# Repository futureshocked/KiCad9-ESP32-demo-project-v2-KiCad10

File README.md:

# KiCad ESP32 demo project, iteration 2 (KiCad 10)

This repository holds the second, corrected iteration of the ESP32 sensor board from my KiCad 9 video lectures, updated and saved in **KiCad 10**. If you want to study the design, modify it or have it manufactured, start here. One known issue remains: automatic reset and download mode do not work, so you upload firmware with the Boot and Reset buttons or through the ESP32-C3's built-in USB. See [Known issue](#known-issue-automatic-reset-and-download-mode-do-not-work).

The first iteration, which matches the original lectures and contains the errors described below, is archived in **[KiCad9-ESP32-demo-project-v1](https://github.com/futureshocked/KiCad9-ESP32-demo-project-v1)**.

## About the project

The board is a battery-powered environmental sensor built around the ESP32-C3. It is a four-layer PCB, about 81 × 54 mm, and includes:

1. An ESP32-C3-WROOM-02 module (U3) with Wi-Fi and Bluetooth LE.
2. A USB-C connector with a CP2102N USB-to-UART bridge (U4), USBLC6-2SC6 ESD protection (U5) and automatic boot/reset circuitry (Q2, Q3).
3. An MCP73871 Li-ion charger with power-path management (U1), a PTC fuse on its output (F2) and an LM1117 3.3 V regulator (VR1).
4. A BME280 temperature, humidity and pressure sensor (U2).
5. A TEMT6000 ambient light sensor (Q1).
6. An electret microphone with a MAX4466 amplifier (U7, MK1) and a gain trimmer (R17).
7. A microSD card slot (J3) and a W25Q32 SPI flash chip (U6).
8. A header for an I2C OLED display, status LEDs, and Boot and Reset buttons.

**You need KiCad 10 or later to open these files.** They are saved in the KiCad 10 file format, which KiCad 9 cannot read. The project files are still named `KiCad 9 ESP32 demo project` so that they match the lectures.

## Two repositories, and why

There are two repositories for this project:

| Repository | Contents | Use it to |
|---|---|---|
| **[KiCad9-ESP32-demo-project-v1](https://github.com/futureshocked/KiCad9-ESP32-demo-project-v1)** | Iteration 1: the original KiCad 9 files with known errors, and a focused repair of U2, U4 and the microphone output | Follow the original lectures and the repair video, and see how the project developed |
| **KiCad9-ESP32-demo-project-v2-KiCad10** (this one) | Iteration 2, corrected and updated in KiCad 10 | Study, modify or manufacture the board |

I have kept both so that the history of the project stays intact, while anyone who wants to experiment with the design, or have it made, has a clean and correct version to start from.

## Status of the issues found in iteration 1

| Issue | Status in iteration 2 |
|---|---|
| 1. PCB out of sync with the schematic (U2, U4, U5, C15) | **Fixed** |
| 2. Microphone output on an ADC2 pin | **Fixed** |
| 3. Automatic reset and download mode (auto-program circuit) | **Partly fixed, still not working.** Q3 is corrected, but DTR is still connected to an input pin. See [Known issue](#known-issue-automatic-reset-and-download-mode-do-not-work). |

1. **The PCB was out of sync with the schematic.** In iteration 1, nine pads on U4 (CP2102N), U5 (USBLC6), U2 (BME280) and C15 were on +3.3V instead of GND, USB D- or VBUS sense. In this version the PCB was updated from the schematic, the stray +3.3V tracks were removed, and those pads were rerouted to their correct nets.
2. **The microphone output was on GPIO5, an ADC2 pin.** Espressif's ESP32-C3 errata recommends against using ADC2. MIC_OUT is now on GPIO0 (ADC1), and CS_SD moved to GPIO5.
3. **Q3 in the auto-program circuit was wired backwards.** Its collector now connects to BOOT and its emitter to DTR, matching Q2 and Espressif's reference circuit. This correction is necessary but not sufficient, because of the issue described next.

The iteration 1 README describes each problem in detail.

## Known issue: automatic reset and download mode do not work

The auto-program circuit (Q2, Q3, R33, R34) is meant to let the CP2102N's DTR and RTS signals reset the ESP32-C3 and put it into download mode, so that you can upload firmware without pressing any buttons. It needs both DTR and RTS to be outputs from the CP2102N.

The CP2102N in this design is the 20-pin QFN package, which has no DTR pin. The net named DTR is connected to U4 pin 15, which is CTS, an input (see table 5.3 of the CP2102N datasheet in `Datasheets/`). Nothing drives the DTR net, so neither automatic reset nor automatic download mode can be relied on. The same mistake is in iteration 1. DRC cannot detect it, because the schematic and PCB agree with each other.

I have not yet decided whether to change the circuit. Until then, use one of these two methods to upload firmware:

1. **Through the USB-C connector and the CP2102N, with the buttons.** Hold **Boot** (S1), press and release **Reset** (S2), then release **Boot**. The ESP32-C3 starts in download mode and you can upload. Press **Reset** afterwards to run the new firmware. Serial monitoring through the CP2102N works normally.
2. **Through the ESP32-C3's built-in USB Serial/JTAG controller.** The ESP32-C3 has its own USB interface on GPIO18 (D-) and GPIO19 (D+). On this board these pins are brought out to header **J5**: pin 3 is D-, pin 4 is D+ and pin 5 is GND. Wire a USB cable's D-, D+ and GND to those pins and power the board from the USB-C connector or the battery. **Do not connect the cable's 5 V wire to J5**: J5 pin 1 is the 3.3 V rail. Through this interface, esptool and the Arduino and ESP-IDF tools can reset the chip and enter download mode without the buttons, and you get a serial console and JTAG debugging as well. For this to keep working, your firmware must not use GPIO18 and GPIO19 as ordinary I/O.

## Other changes from iteration 1

1. A PTC fuse (F2) on the +5 V output of the charger.
2. A trimmer (R17) to adjust the microphone gain, with new values for R30 (1 kΩ), R31 (22 kΩ) and C19 (10 µF).
3. The light sensor was rearranged so that its output rises with light: Q1's collector goes to +3.3V and R23 pulls the output down to GND.
4. Three extra capacitors: C23 (100 nF decoupling) and C24 and C25 (10 nF filtering on the light sensor signal).
5. The Boot and Reset buttons (S1, S2) were rotated 180°, and the right edge of the board moved about 0.8 mm.

## Design check status

A DRC with **Test for parity between PCB and schematic** enabled reports no errors and no unconnected pads. DRC only compares the PCB with the schematic, so it cannot detect design errors like the DTR problem above. A few warnings remain. None of them affect how the circuit works:

1. **S1 and S2 parity warnings.** The schematic symbols for the Boot and Reset buttons still name the E-Switch TL3305 footprint, while the PCB uses the TE USLPT2819. The two parts number their pins differently, so DRC reports four pad net conflicts. According to the USLPT2819 datasheet, pins 1 and 2 are connected internally, as are pins 3 and 4, and the switch closes between the two pairs. On the PCB, pins 1 and 2 go to GND and pins 3 and 4 go to BOOT or EN, which is correct for the switch that is actually fitted.
2. **USB D- track width.** D- is routed at 0.254 mm and D+ at 0.2 mm. At USB 2.0 full speed (12 Mbit/s) this makes no practical difference, but the two lines are not a matched differential pair.
3. **Housekeeping warnings.** These are library footprint differences, unmirrored text on the back layer, three logo footprints without schematic symbols, two empty description fields, and an "exclude from BOM" setting on J3 that differs between schematic and PCB.

## Files

1. `KiCad 9 ESP32 demo project.kicad_pro`, `.kicad_sch` and `.kicad_pcb`: the KiCad project, with the sub-sheets `esp32-c3-02.kicad_sch`, `sensors.kicad_sch` and `user_interface.kicad_sch`.
2. `Libraries/`: project-specific symbols, footprints and 3D models.
3. `Gerbers/`: Gerber and Excellon drill files, generated from this PCB with the board's saved plot settings.
4. `BOM2.ods`: the bill of materials.
5. `Datasheets/`: datasheets for the main components.
6. `3Dmodel.stl`: an STL export of the board's 3D model, made in March 2025, before the final KiCad 10 edits.

## License

Copyright © 2025–2026, Peter Dalmaris. Licensed under the CERN-OHL-S v2.0. See [LICENSE](LICENSE).

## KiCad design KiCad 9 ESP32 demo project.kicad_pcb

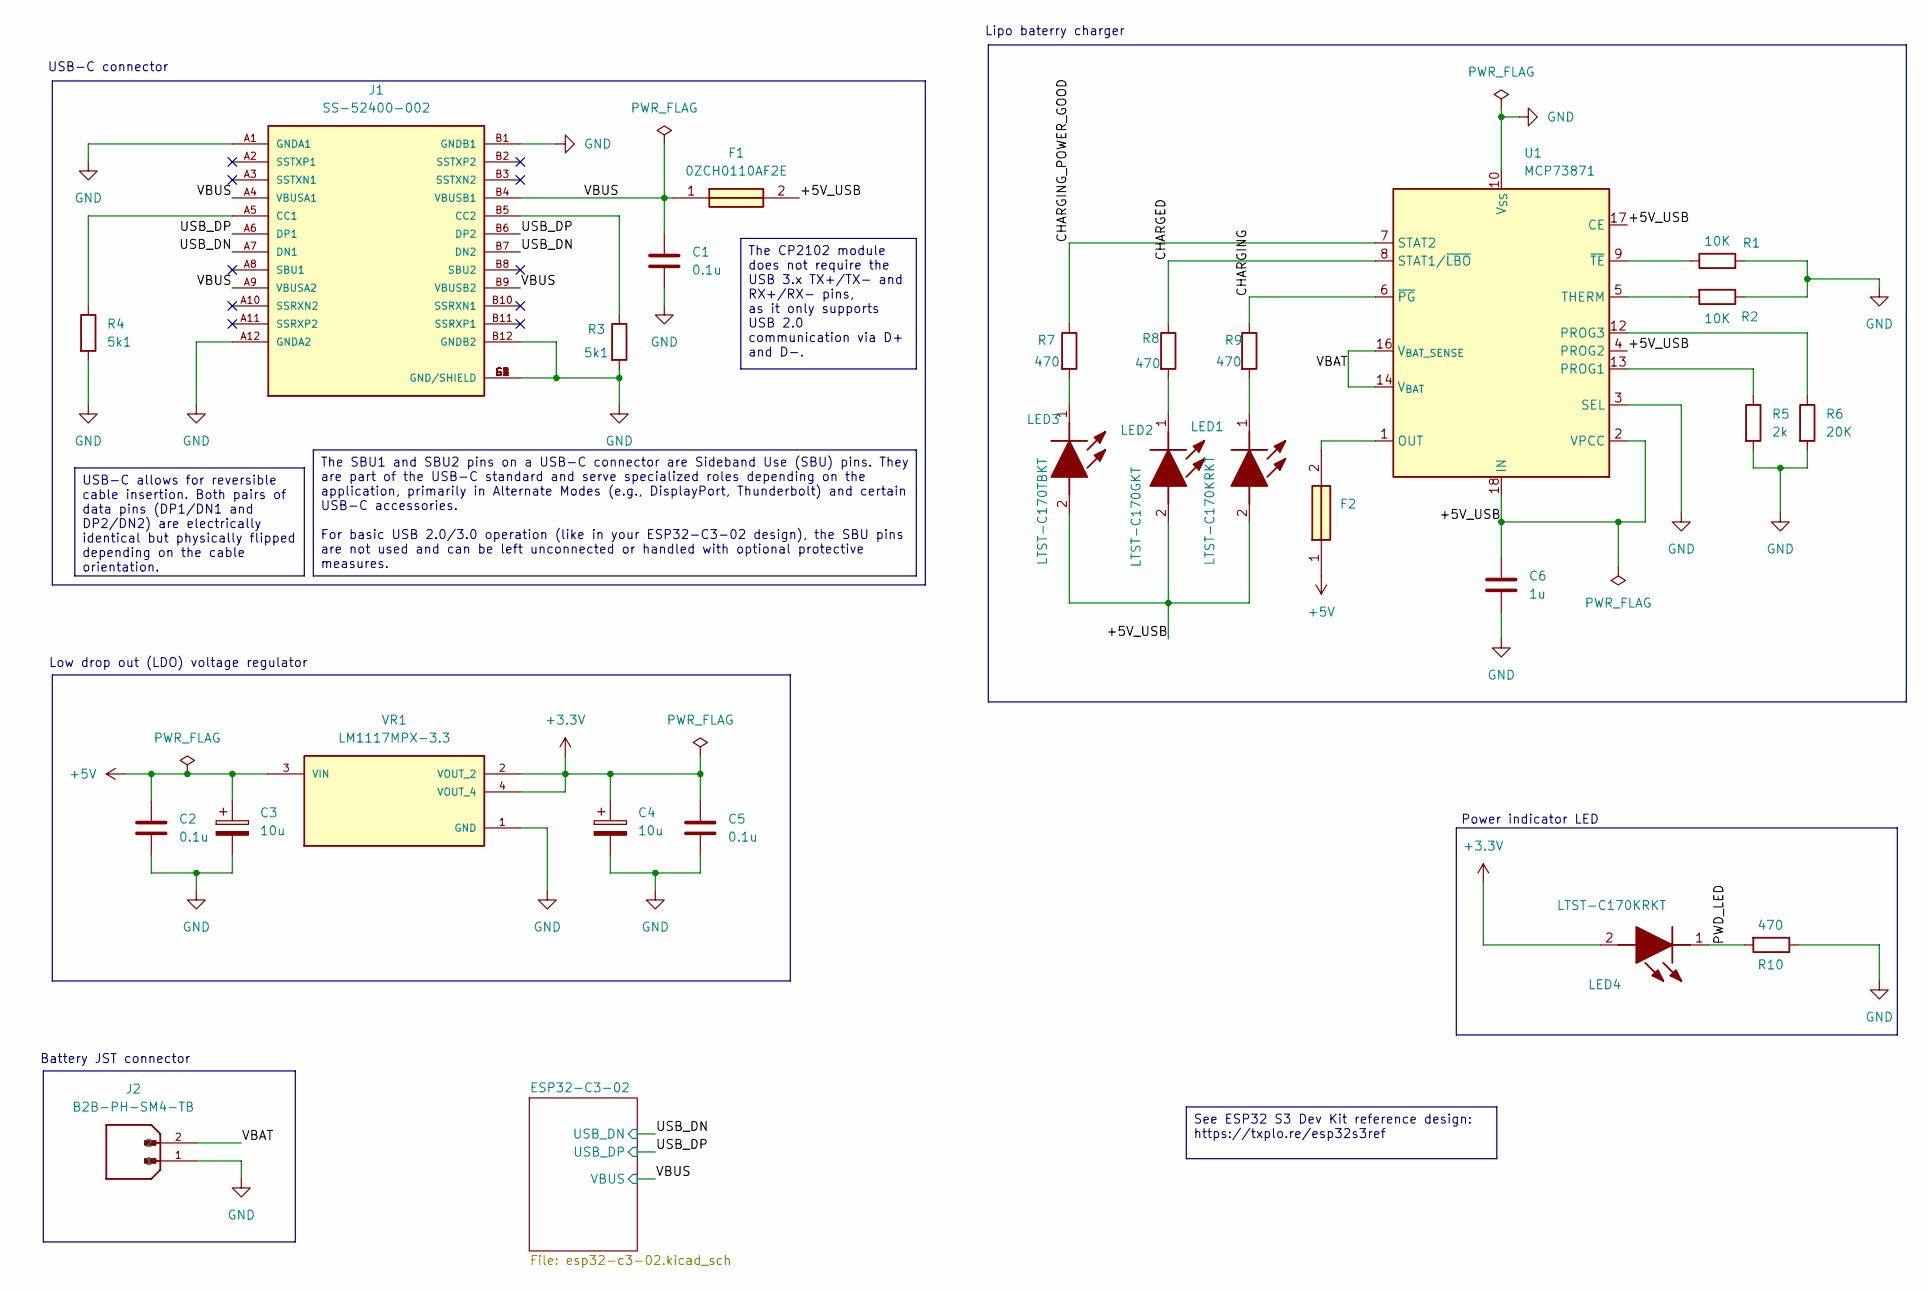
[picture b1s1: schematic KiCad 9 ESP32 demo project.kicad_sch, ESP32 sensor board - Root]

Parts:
C1, C2, C5: 0.1u; C_0805_2012Metric
C3, C4: 10u; T491A
C6: 1u; C_0805_2012Metric
F1, F2: 0ZCH0110AF2E; FUSC3226X100N; Manufacturer_Part_Number 0ZCH0110AF2E
J1: SS-52400-002; BELFUSE_SS-52400-002; PARTREV A0
J2: B2B-PH-SM4-TB; JST_B2B-PH-SM4-TB; PARTREV N/A
LED1, LED4: LTST-C170KRKT; LEDC2012X120N; Manufacturer_Part_Number LTST-C170KRKT; Mouser Part Number 859-LTST-C170KRKT
LED2: LTST-C170GKT; LEDC2012X120N; Manufacturer_Part_Number LTST-C170GKT; Mouser Part Number 859-LTST-C170GKT
LED3: LTST-C170TBKT; LEDC2012X120N; Manufacturer_Part_Number LTST-C170TBKT; Mouser Part Number 859-LTST-C170TBKT
R1, R2: 10K; R_0805_2012Metric
R3, R4: 5k1; R_0805_2012Metric
R5: 2k; R_0805_2012Metric
R6: 20K; R_0805_2012Metric
R7, R8, R9, R10: 470; R_0805_2012Metric
U1: MCP73871; QFN-20-1EP_4x4mm_P0.5mm_EP2.5x2.5mm
VR1: LM1117MPX-3.3; VREG_LM1117MPX-3.3

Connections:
+3.3V: C4.1, C5.1, LED4.2 (A), VR1.2 (VOUT_2), VR1.4 (VOUT_4); also elsewhere on the board
+5V: C2.1, C3.1, F2.1, VR1.3 (VIN)
/+5V_USB: C6.1, F1.2, LED1.2 (A), LED2.2 (A), LED3.2 (A), U1.2 (VPCC), U1.4 (PROG2), U1.17 (CE), U1.18 (IN), U1.19 (IN)
/CHARGED: R8.1, U1.8 (STAT1/~LBO)
/CHARGING: R9.1, U1.6 (~PG)
/CHARGING_POWER_GOOD: R7.1, U1.7 (STAT2)
/PWD_LED: LED4.1 (K), R10.2
/USB_DN: J1.A7 (DN1), J1.B7 (DN2); also elsewhere on the board
/USB_DP: J1.A6 (DP1), J1.B6 (DP2); also elsewhere on the board
/VBAT: J2.2, U1.14 (V_{BAT}), U1.15 (V_{BAT}), U1.16 (V_{BAT_SENSE})
/VBUS: C1.1, F1.1, J1.A4 (VBUSA1), J1.A9 (VBUSA2), J1.B4 (VBUSB1), J1.B9 (VBUSB2); also elsewhere on the board
unnamed: F2.2, U1.1 (OUT), U1.20 (OUT)
unnamed: J1.A5 (CC1), R4.1
unnamed: J1.B5 (CC2), R3.1
unnamed: LED1.1 (K), R9.2
unnamed: LED2.1 (K), R8.2
unnamed: LED3.1 (K), R7.2
unnamed: R5.1, U1.13 (PROG1)
unnamed: R6.1, U1.12 (PROG3)
unnamed: R2.2, U1.5 (THERM)
unnamed: R1.1, U1.9 (~TE)

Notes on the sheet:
Lipo baterry charger
Low drop out (LDO) voltage regulator
Power indicator LED
Battery JST connector
USB-C connector
See ESP32 S3 Dev Kit reference design: https://txplo.re/esp32s3ref
The CP2102 module does not require the USB 3.x TX+/TX- and RX+/RX- pins, as it only supports USB 2.0 communication via D+ and D-.
USB-C allows for reversible cable insertion. Both pairs of data pins (DP1/DN1 and DP2/DN2) are electrically identical but physically flipped depending on the cable orientation.
The SBU1 and SBU2 pins on a USB-C connector are Sideband Use (SBU) pins. They are part of the USB-C standard and serve specialized roles depending on the application, primarily in Alternate Modes (e.g., DisplayPort, Thunderbolt) and certain USB-C accessories. For basic USB 2.0/3.0 operation (like i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

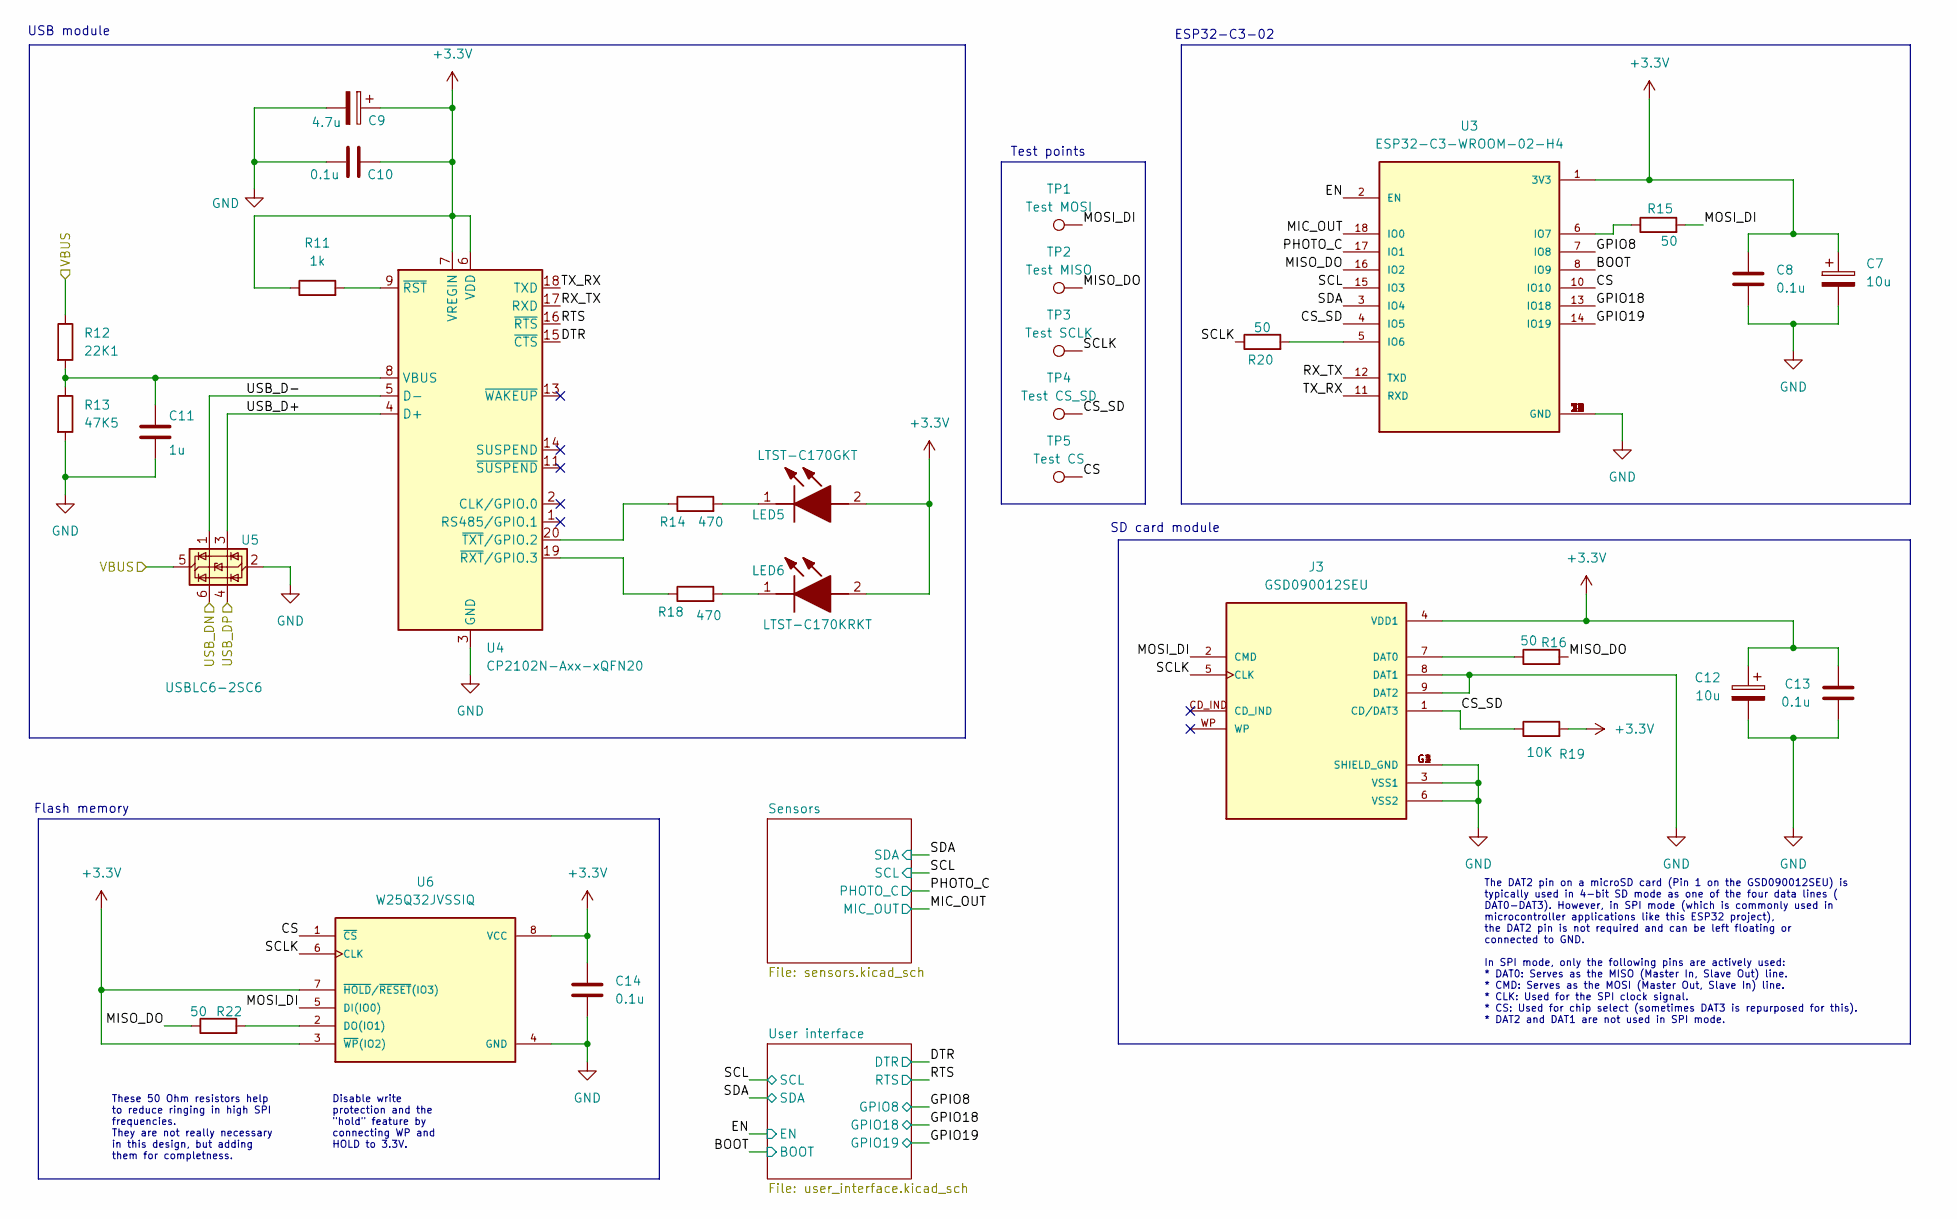
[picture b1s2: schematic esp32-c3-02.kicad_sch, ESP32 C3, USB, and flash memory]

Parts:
C7, C12: 10u; T491A
C8, C10, C13, C14: 0.1u; C_0805_2012Metric
C9: 4.7u; T491A
C11: 1u; C_0805_2012Metric
J3: GSD090012SEU; AMPHENOL_GSD090012SEU; PARTREV E
LED5: LTST-C170GKT; LEDC2012X120N; Manufacturer_Part_Number LTST-C170GKT; Mouser Part Number 859-LTST-C170GKT
LED6: LTST-C170KRKT; LEDC2012X120N; Manufacturer_Part_Number LTST-C170KRKT; Mouser Part Number 859-LTST-C170KRKT
R11: 1k; R_0805_2012Metric
R12: 22K1; R_0805_2012Metric
R13: 47K5; R_0805_2012Metric
R14, R18: 470; R_0805_2012Metric
R15, R16, R20, R22: 50; R_0805_2012Metric
R19: 10K; R_0805_2012Metric
TP1: Test MOSI; TestPoint_Pad_D1.0mm
TP2: Test MISO; TestPoint_Pad_D1.0mm
TP3: Test SCLK; TestPoint_Pad_D1.0mm
TP4: Test CS_SD; TestPoint_Pad_D1.0mm
TP5: Test CS; TestPoint_Pad_D1.0mm
U3: ESP32-C3-WROOM-02-H4; MODULE_ESP32-C3-WROOM-02-H4
U4: CP2102N-Axx-xQFN20; SiliconLabs_QFN-20-1EP_3x3mm_P0.5mm_EP1.8x1.8mm
U5: USBLC6-2SC6; SOT-23-6
U6: W25Q32JVSSIQ; SOIC127P790X216-8N; M_PART_NUMBER W25QXX

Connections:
+3.3V: C7.1, C8.1, C9.1, C10.2, C12.1, C13.1, C14.1, J3.4 (VDD1), LED5.2 (A), LED6.2 (A), R11.1, R19.2, U3.1 (3V3), U4.6 (VDD), U4.7 (VREGIN), U6.3 (~WP(IO2)), U6.7 (~HOLD/~RESET(IO3)), U6.8 (VCC); also elsewhere on the board
/ESP32-C3-02/CS: TP5.1, U3.10 (IO10), U6.1 (~CS)
/ESP32-C3-02/CS_SD: J3.1 (CD/DAT3), R19.1, TP4.1, U3.4 (IO5)
/ESP32-C3-02/DTR: U4.15 (~CTS); also elsewhere on the board
/ESP32-C3-02/GPIO8: U3.7 (IO8); also elsewhere on the board
/ESP32-C3-02/GPIO18: U3.13 (IO18); also elsewhere on the board
/ESP32-C3-02/GPIO19: U3.14 (IO19); also elsewhere on the board
/ESP32-C3-02/MIC_OUT: U3.18 (IO0); also elsewhere on the board
/ESP32-C3-02/MISO_DO: R16.2, R22.1, TP2.1, U3.16 (IO2)
/ESP32-C3-02/MOSI_DI: J3.2 (CMD), R15.2, TP1.1, U6.5 (DI(IO0))
/ESP32-C3-02/PHOTO_C: U3.17 (IO1); also elsewhere on the board
/ESP32-C3-02/RTS: U4.16 (~RTS); also elsewhere on the board
/ESP32-C3-02/RX_TX: U3.12 (TXD), U4.17 (RXD)
/ESP32-C3-02/SCL: U3.15 (IO3); also elsewhere on the board
/ESP32-C3-02/SCLK: J3.5 (CLK), R20.1, TP3.1, U6.6 (CLK)
/ESP32-C3-02/SDA: U3.3 (IO4); also elsewhere on the board
/ESP32-C3-02/TX_RX: U3.11 (RXD), U4.18 (TXD)
/ESP32-C3-02/USB_D+: U4.4 (D+), U5.3 (I/O2)
/ESP32-C3-02/USB_D-: U4.5 (D-), U5.1 (I/O1)
/USB_DN: U5.6 (I/O1); also elsewhere on the board
/USB_DP: U5.4 (I/O2); also elsewhere on the board
/VBUS: R12.1, U5.5 (VBUS); also elsewhere on the board
unnamed: J3.7 (DAT0), R16.1
unnamed: LED5.1 (K), R14.2
unnamed: LED6.1 (K), R18.2
unnamed: R20.2, U3.5 (IO6)
unnamed: R15.1, U3.6 (IO7)
unnamed: C11.1, R12.2, R13.1, U4.8 (VBUS)
unnamed: R11.2, U4.9 (~RST)
unnamed: R18.1, U4.19 (~RXT/GPIO.3)
unnamed: R14.1, U4.20 (~TXT/GPIO.2)
unnamed: R22.2, U6.2 (DO(IO1))

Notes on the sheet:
USB module
SD card module
Flash memory
ESP32-C3-02
Test points
These 50 Ohm resistors help to reduce ringing in high SPI frequencies. They are not really necessary in this design, but adding them for completness.
The DAT2 pin on a microSD card (Pin 1 on the GSD090012SEU) is typically used in 4-bit SD mode as one of the four data lines ( DAT0-DAT3). However, in SPI mode (which is commonly used in microcontroller applications like this ESP32 project), the DAT2 pin is not required and can be left floating or c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
Disable write protection and the "hold" feature by connecting WP and HOLD to 3.3V.

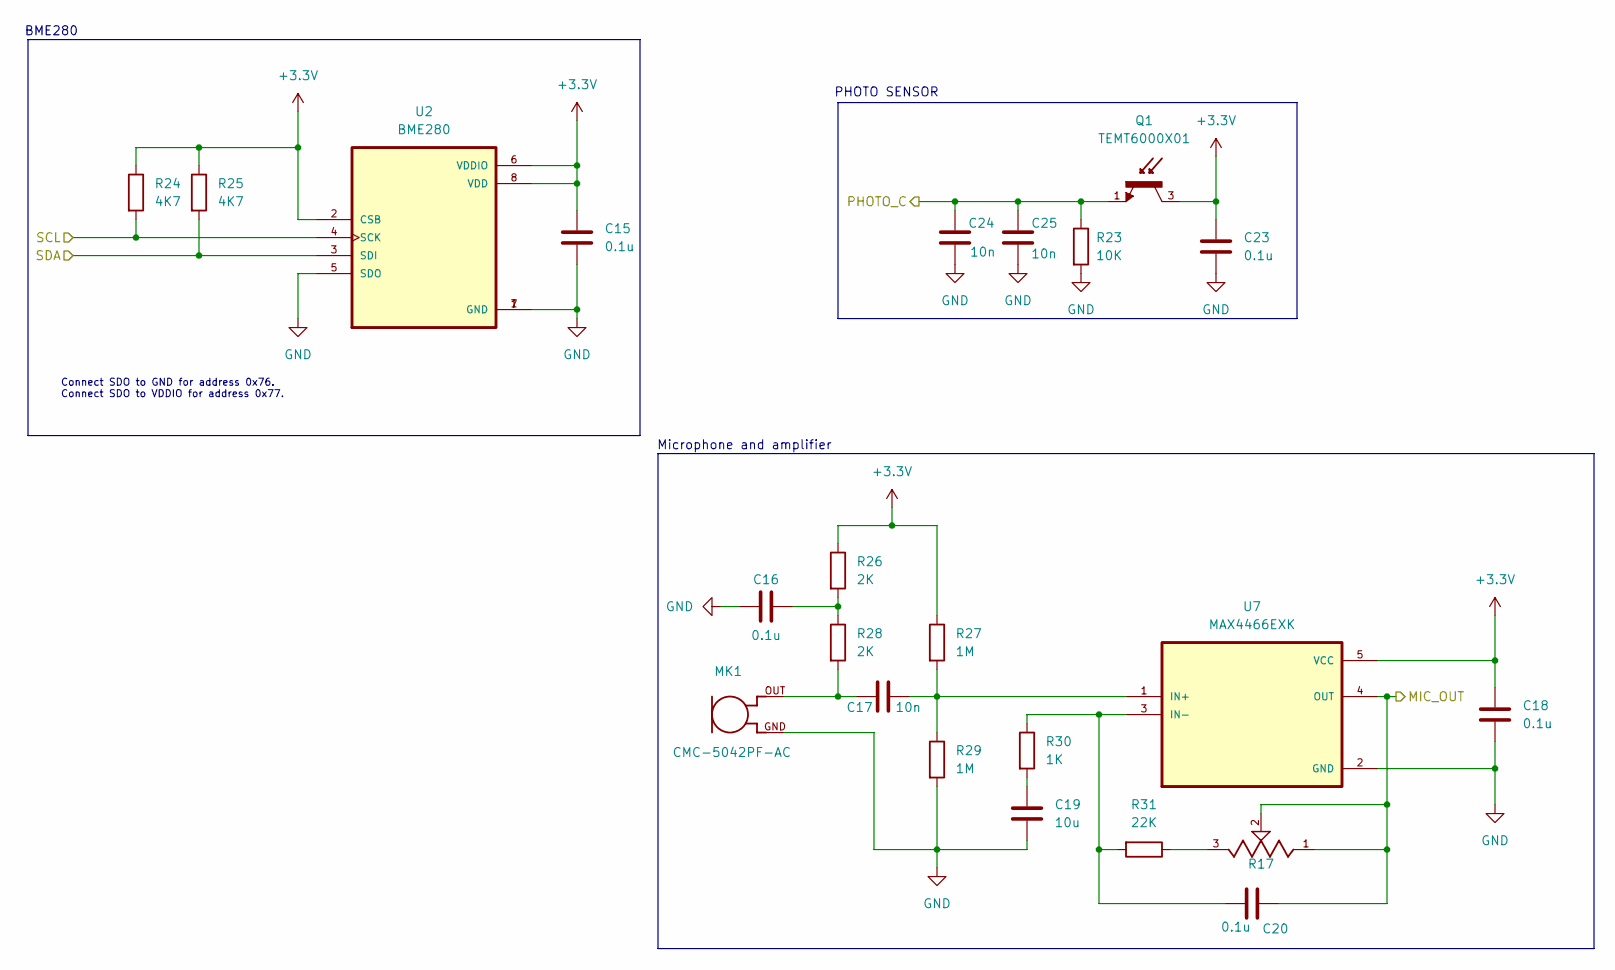
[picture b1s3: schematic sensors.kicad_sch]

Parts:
C15, C16, C18, C20, C23: 0.1u; C_0805_2012Metric
C17, C24, C25: 10n; C_0805_2012Metric
C19: 10u; C_0805_2012Metric
MK1: CMC-5042PF-AC; CUI_CMC-5042PF-AC
Q1: TEMT6000X01; TRANS_TEMT6000X01; PARTREV 1.9
R17: 35WR100KLFTR; TRIM_35WR100KLFTR; PARTREV D
R23: 10K; R_0805_2012Metric
R24, R25: 4K7; R_0805_2012Metric
R26, R28: 2K; R_0805_2012Metric
R27, R29: 1M; R_0805_2012Metric
R30: 1K; R_0805_2012Metric
R31: 22K; R_0805_2012Metric
U2: BME280; PSON65P250X250X100-8N
U7: MAX4466EXK; SOT65P210X110-5N

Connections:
+3.3V: C15.1, C18.1, C23.1, Q1.3, R24.1, R25.1, R26.1, R27.1, U2.2 (CSB), U2.6 (VDDIO), U2.8 (VDD), U7.5 (VCC); also elsewhere on the board
/ESP32-C3-02/MIC_OUT: C20.1, R17.1, R17.2, U7.4 (OUT); also elsewhere on the board
/ESP32-C3-02/PHOTO_C: C24.1, C25.1, Q1.1, R23.1; also elsewhere on the board
/ESP32-C3-02/SCL: R24.2, U2.4 (SCK); also elsewhere on the board
/ESP32-C3-02/SDA: R25.2, U2.3 (SDI); also elsewhere on the board
unnamed: C16.1, R26.2, R28.1
unnamed: C17.2, MK1.OUT, R28.2
unnamed: C19.1, R30.2
unnamed: R17.3, R31.1
unnamed: C17.1, R27.2, R29.1, U7.1 (IN+)
unnamed: C20.2, R30.1, R31.2, U7.3 (IN-)

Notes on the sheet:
Microphone and amplifier
PHOTO SENSOR
BME280
Connect SDO to GND for address 0x76. Connect SDO to VDDIO for address 0x77.

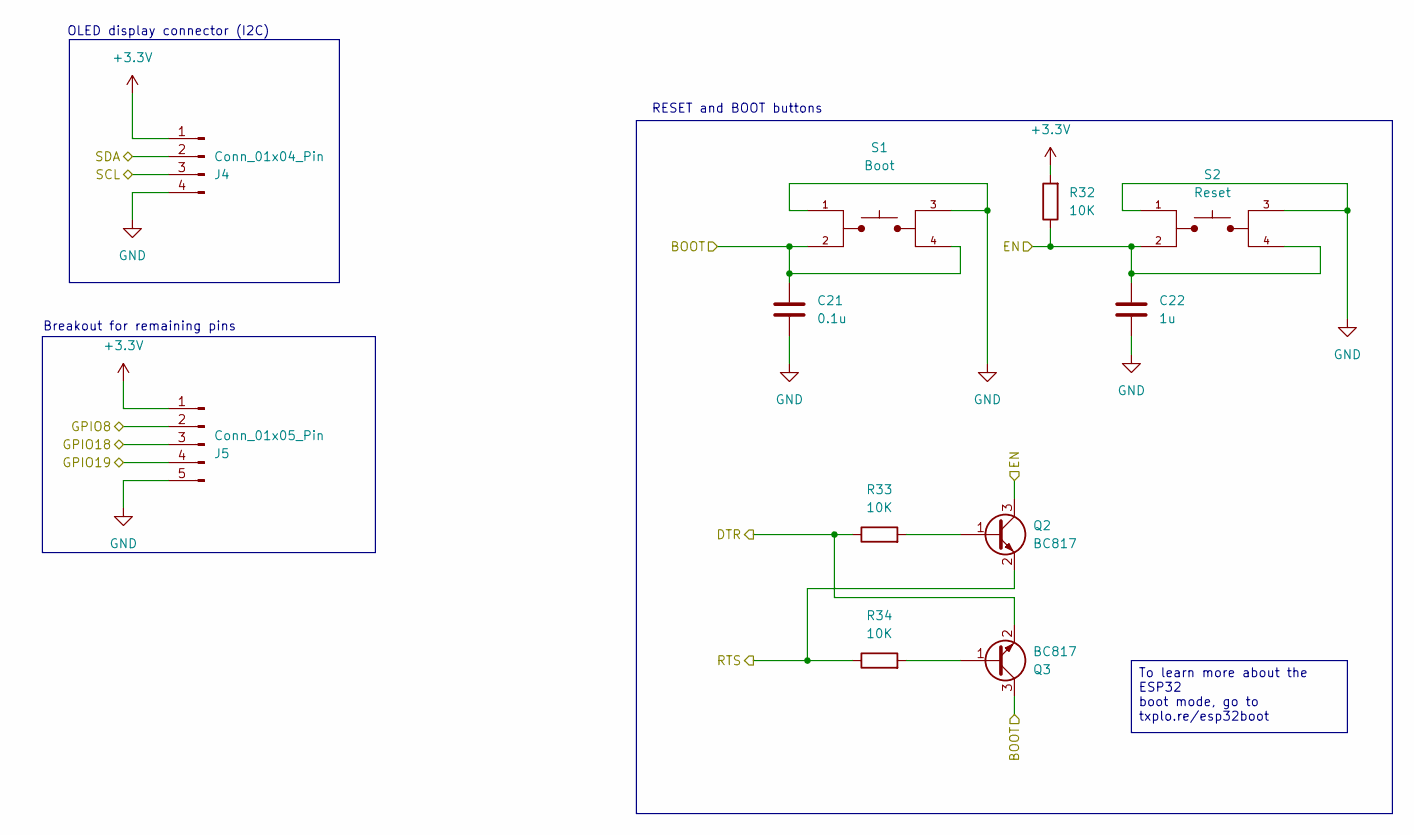
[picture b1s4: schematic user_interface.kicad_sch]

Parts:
C21: 0.1u; C_0805_2012Metric
C22: 1u; C_0805_2012Metric
J4: Conn_01x04_Pin; PinHeader_1x04_P2.54mm_Vertical
J5: Conn_01x05_Pin; PinHeader_1x05_P2.54mm_Vertical
Q2, Q3: BC817; SOT-23
R32, R33, R34: 10K; R_0805_2012Metric
S1: Boot; SW_TL3305AF260QG; PARTREV C
S2: Reset; SW_TL3305AF260QG; PARTREV C

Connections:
+3.3V: J4.1, J5.1, R32.2; also elsewhere on the board
/ESP32-C3-02/DTR: Q3.2 (E), R33.1; also elsewhere on the board
/ESP32-C3-02/GPIO8: J5.2; also elsewhere on the board
/ESP32-C3-02/GPIO18: J5.3; also elsewhere on the board
/ESP32-C3-02/GPIO19: J5.4; also elsewhere on the board
/ESP32-C3-02/RTS: Q2.2 (E), R34.1; also elsewhere on the board
/ESP32-C3-02/SCL: J4.3; also elsewhere on the board
/ESP32-C3-02/SDA: J4.2; also elsewhere on the board
unnamed: Q2.1 (B), R33.2
unnamed: Q3.1 (B), R34.2

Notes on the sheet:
Breakout for remaining pins
RESET and BOOT buttons
OLED display connector (I2C)
To learn more about the ESP32 boot mode, go to txplo.re/esp32boot

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
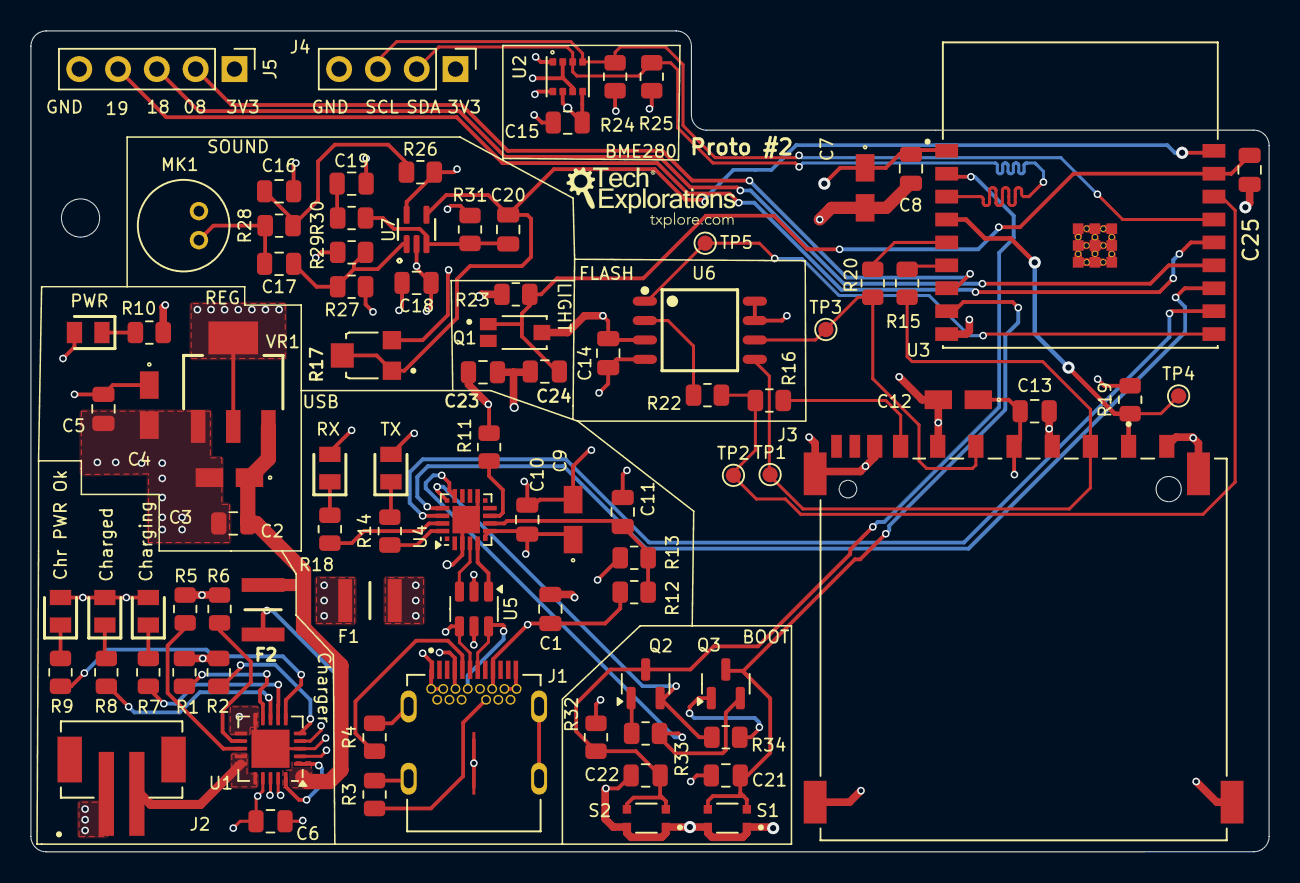
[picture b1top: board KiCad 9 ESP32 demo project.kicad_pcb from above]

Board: 4 copper layers, 81.1 x 53.8 mm, 90 parts (0 on the bottom side), 60 nets.
